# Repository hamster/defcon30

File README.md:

# defcon 30 SAOs

Hello!  I'm [@hamster](https://twitter.com/hamster) and I was honored this year to be able to make a couple of SAOs for defcon.  I tried to make these simple and fun, and I hope you enjoy them.

The first one is the [SAO Modem 1.69bis](modem), which is a throwback to the days of the external Courier modem screaming away at the internet.  It does not actually communicate with the internet, but it sure is blinky.

The second one is [SAO Jack](jack), a simple learn to solder kit with the spirit of defcon in the artwork.

I hope you enjoy, and let [me](https://twitter.com/hamster) know what you think!

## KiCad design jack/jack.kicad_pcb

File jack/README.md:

# Jack SAO

Jack is a simple SAO soldering kit.  Consisting of 4 LEDs in two colors, two resistors, and a connector, it's an easy way to learn how to solder.

To start, dump your kit out on the table and make sure you have all the parts pictured.  You'll need a soldering iron, solder, and a pair of wire cutters.

Locate the LEDs. Note that typically the LED is cast with a flat spot to indicate the cathode (or negative) terminal.  However, these small LEDS instead have the shorter leg as the cathode.

Look at the back of the PCB.  Note the diagram for the LEDS - the short legs of the LEDs will all go towards the top of the PCB.  This is also the square holes on the board.

It doesn't matter which color you put where.  Get crazy with it.  You can even leave the legs a little long and bend the LEDs to point out.  Whatever you want to do.

Insert the LEDs and flip over the PCB.  Make sure the short legs are going through the square holes.  Solder the legs into place.

Now that the LEDs are in place, you can clip the legs off with your wire cutters.

Locate the two resistors.  Bend their legs down and insert them from the back into the holes above and below the two rectangles on the lower left as shown.

Now flip the board over and push the resistors flat.  It helps here to bend the legs out so they can't slip while you are soldering.  Solder the legs down, and clip off the excess legs.

Finally, we need to install the SAO connector.  Locate the connector, and note on the back that the notch or tab needs to go 'up'.

Flip the board over, and solder the connector on.  I like to solder one pin, and then lift the board and pinch the connector while re-applying heat so that the connector is mounted flat, before finishing the solder of the rest of the pins.

You're all done!  Enjoy your SAO and let [me](https://twitter.com/hamster) know what you think!

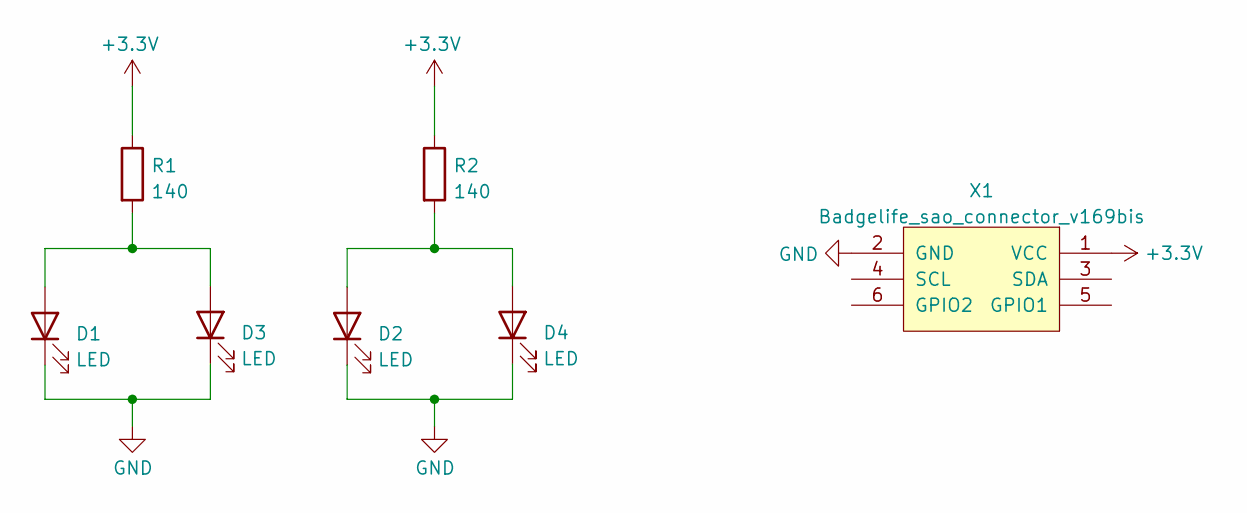
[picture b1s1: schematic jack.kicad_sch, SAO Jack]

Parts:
D1, D2, D3, D4: LED; LED_D3.0mm
R1, R2: 140; R_Axial_DIN0204_L3.6mm_D1.6mm_P7.62mm_Horizontal
X1: Badgelife_sao_connector_v169bis; Badgelife-Shitty-v1.69bis

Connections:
+3V3: R1.1, R2.1, X1.1 (VCC)
GND: D1.1 (K), D2.1 (K), D3.1 (K), D4.1 (K), X1.2 (GND)
unnamed: D1.2 (A), D3.2 (A), R1.2
unnamed: D2.2 (A), D4.2 (A), R2.2

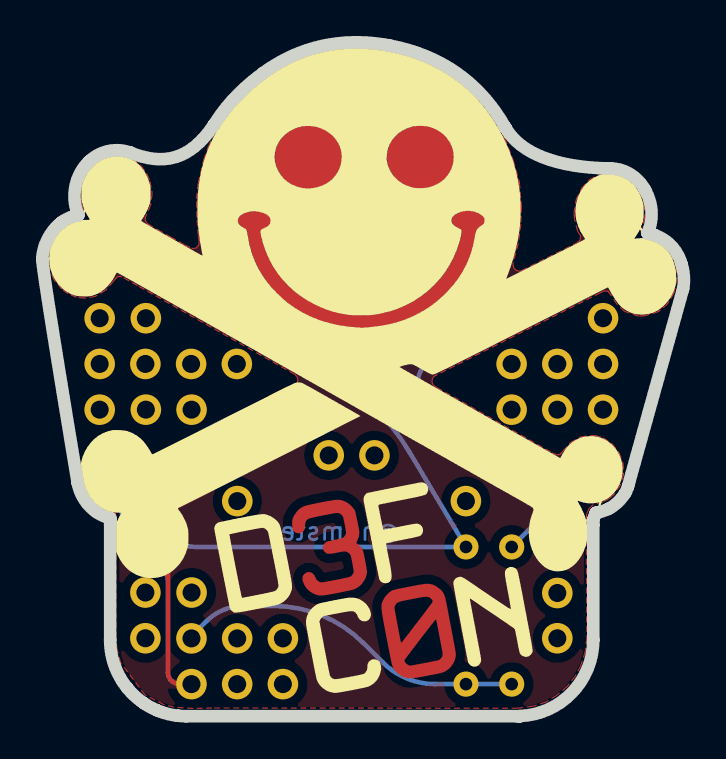
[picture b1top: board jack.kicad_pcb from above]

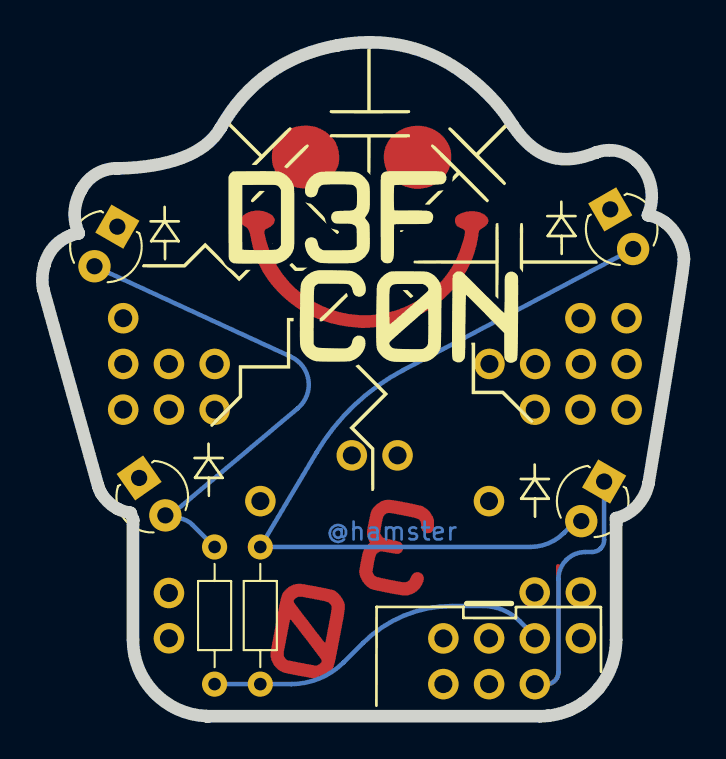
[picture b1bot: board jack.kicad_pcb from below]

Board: 2 copper layers, 35.6 x 37.4 mm, 7 parts (2 on the bottom side), 4 nets.

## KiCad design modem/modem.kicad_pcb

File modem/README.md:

# SAO Modem 1.69bis

This SAO is designed to add some blinky lights to your badge, calling back to the days of an external Courier modem screaming away on the internet.

There are 6 lights:

- AA - Power, lights when 3.3v is present
- OH - Flashes on I2C SCL activity
- SD - Flashes on I2C SDA activity
- RTS - Flashes on GPIO1 activity
- CTS - Flashes on GPIO2 activity
- SYN - Connected to a free pad on the back, you choose what it does

The I2C inputs were selected to minimize load on the I2C bus, but this SAO might cause issues with badges with high speed I2C.  In that case, you can swap R7 and R8 for higher value resistors.

You will need to solder on the SAO connector.  Note that the notch or tab goes towards the top.  See photo for reference.  I like to insert the connector, solder one pin, then pinch the connector to the board with my fingers and re-heat this connection so that the connector snaps flat to the board before I solder on the rest of the pins.

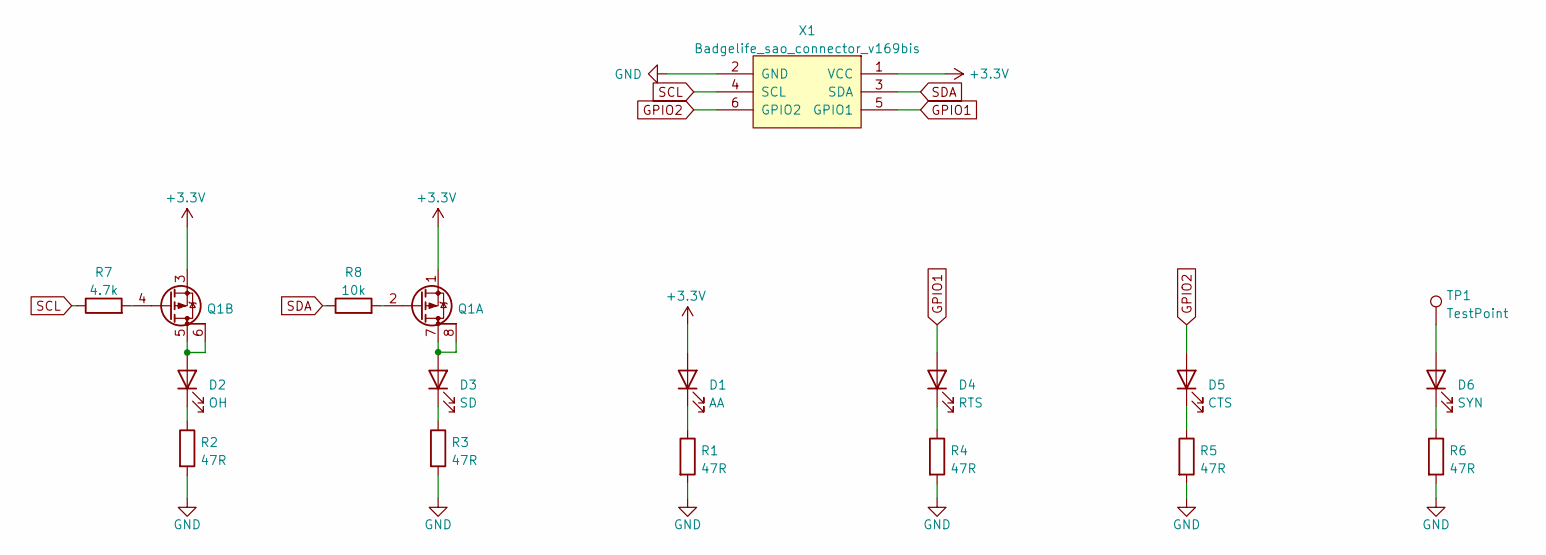
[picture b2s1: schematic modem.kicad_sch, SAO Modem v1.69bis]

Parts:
D1: AA; LED_0805_2012Metric
D2: OH; LED_0805_2012Metric
D3: SD; LED_0805_2012Metric
D4: RTS; LED_0805_2012Metric
D5: CTS; LED_0805_2012Metric
D6: SYN; LED_0805_2012Metric
Q1: Q_Dual_PMOS_S1G1D2S2G2D1; SOIC-8_3.9x4.9mm_P1.27mm
R1, R2, R3, R4, R5, R6: 47R; R_0603_1608Metric
R7: 4.7k; R_0603_1608Metric
R8: 10k; R_0603_1608Metric
TP1: TestPoint; TestPoint_Pad_D2.0mm
X1: Badgelife_sao_connector_v169bis; Badgelife-Shitty-v1.69bis

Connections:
+3V3: D1.2 (A), Q1.1 (S), Q1.3 (S), X1.1 (VCC)
GND: R1.2, R2.2, R3.2, R4.2, R5.2, R6.2, X1.2 (GND)
GPIO1: D4.2 (A), X1.5 (GPIO1)
GPIO2: D5.2 (A), X1.6 (GPIO2)
unnamed: D1.1 (K), R1.1
unnamed: D2.1 (K), R2.1
unnamed: D2.2 (A), Q1.5 (D), Q1.6 (G)
unnamed: D3.1 (K), R3.1
unnamed: D3.2 (A), Q1.7 (D), Q1.8 (G)
unnamed: D4.1 (K), R4.1
unnamed: D5.1 (K), R5.1
unnamed: D6.1 (K), R6.1
unnamed: D6.2 (A), TP1.1
unnamed: Q1.2 (G), R8.2
unnamed: Q1.4 (G), R7.2
SCL: R7.1, X1.4 (SCL)
SDA: R8.1, X1.3 (SDA)

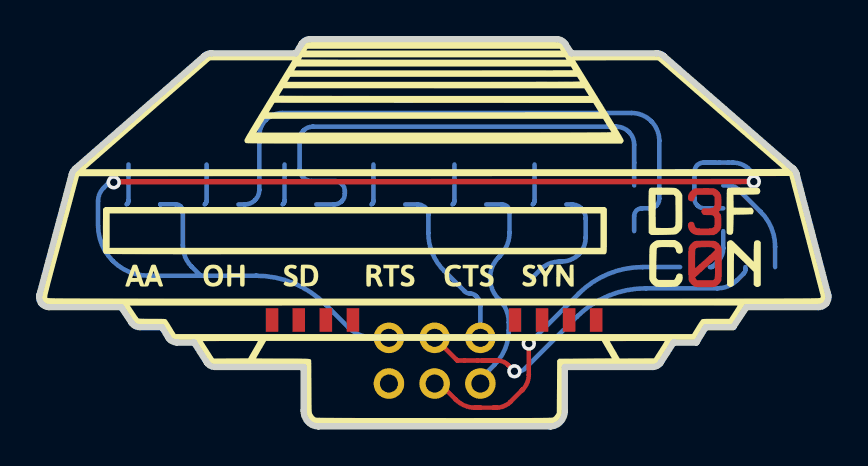
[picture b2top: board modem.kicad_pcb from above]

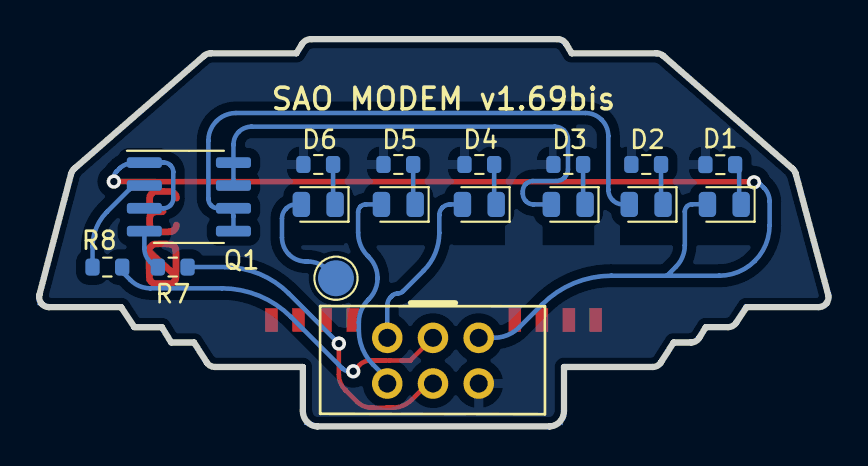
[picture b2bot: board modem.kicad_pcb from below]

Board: 2 copper layers, 43.9 x 21.5 mm, 19 parts (16 on the bottom side), 17 nets.

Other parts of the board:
tab: Tab
tab#2: Tab

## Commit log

2022-08-10 Initial commit of the as-built designs, build instructions
2022-08-10 Adding build instructions for the SAO modem
2022-08-10 Fixed image filename
2022-08-10 Fix bad image URLs
